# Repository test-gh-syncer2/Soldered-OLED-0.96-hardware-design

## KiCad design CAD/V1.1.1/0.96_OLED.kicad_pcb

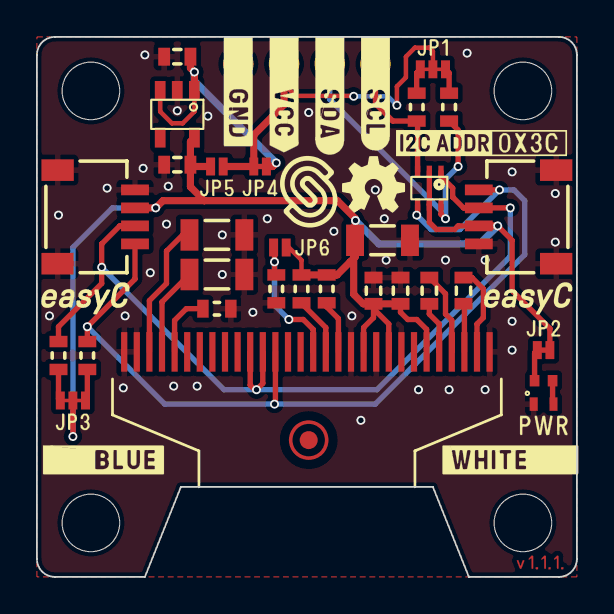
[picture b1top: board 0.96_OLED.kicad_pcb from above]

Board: 2 copper layers, 30.0 x 30.0 mm, 36 parts (1 on the bottom side), 24 nets.

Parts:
C1, C2, C5, C8: 2u2; 0603C
C3, C7, C9: 10u; 1206C
C4: 1u; 0603C
C6: 100n; 0603C
D1: purple; 0402LED
FD1: FIDUCIAL; FIDUCIAL_23
H1, H2, H3, H4: HOLE_3.2mm
JP1, JP3: SMD_JUMPER_3_PAD_TRACE
JP2, JP4: SMD-JUMPER-CONNECTED_TRACE_SLODERMASK
JP5, JP6: SMD_JUMPER
K1, K2: easyC-SMD; easyC-connector
K3: HEADER_MALE_4X1
R1, R2, R3, R4, R6, R7, R8: 10k; 0603R
R5: 2k2; 0402R
R9: 390k; 0603R
U1: NMOS-DUAL; SOT-363
U2: SE5218; SOT-23-5
U3: OLED_GME12864_30p; OLED_GME128x64_30p

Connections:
3V3: C2.2, C3.1, C4.1, C6.1, JP2.1, JP3.2, JP5.2, JP6.2, K1.3 (3V3), K2.3 (3V3), R6.2, R7.2, U1.2 (G2), U1.5 (G1), U2.5 (VOUT), U3.6 (VBAT), U3.9 (VDD), U3.11 (BS1)
CS: R6.1, U3.13 (CSn)
GND: C1.1, C2.1, C3.2, C4.2, C6.2, C7.2, C9.2, D1.2 (K), K1.4 (GND), K1.5 (SHIELD), K2.4 (GND), K2.5 (SHIELD), K3.1, R8.1, R9.2, U2.2 (GND), U3.1 (N.C.(GND)), U3.8 (VSS), U3.10 (BS0), U3.12 (BS2), U3.29 (VLSS), U3.30 (N.C.(GND))
unnamed: C1.2, JP4.1, U2.1 (VIN), U2.3 (EN)
unnamed: C5.1, U3.5 (C1N)
unnamed: C5.2, U3.4 (C1P)
unnamed: C7.1, U3.27 (VCOMH)
unnamed: C8.1, U3.3 (C2N)
unnamed: C8.2, U3.2 (C2P)
unnamed: C9.1, U3.28 (VCC)
unnamed: D1.1 (A), R5.2
unnamed: JP2.2, R5.1
unnamed: R9.1, U3.26 (IREF)
unnamed: JP6.1, R8.2, U3.15 (D/Cn)
RST: R7.1, U3.14 (RESn)
SCL3,3: K1.1 (SCL), K2.1 (SCL), R4.1, U1.4 (S1), U3.18 (D0)
SCL5: K3.4, R2.2, U1.3 (D1)
SCL_PULL3,3: JP3.1, R4.2
SCL_PULL5: JP1.1, R2.1
SDA3,3: K1.2 (SDA), K2.2 (SDA), R1.2, U1.1 (S2), U3.19 (D1), U3.20 (D2)
SDA5: K3.3, R3.1, U1.6 (D2)
SDA_PULL3,3: JP3.3, R1.1
SDA_PULL5: JP1.3, R3.2
VCC: JP1.2, JP4.2, JP5.1, K3.2

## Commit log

2021-09-23 Syncing to git
2021-09-23 Updating open source files.
